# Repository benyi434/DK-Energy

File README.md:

# DK-Energy
DK Energy - Powerbank solar portátil con 18650, TP4056, MT3608, PIC16F887 y LCD 16x2. Proyecto integrador IPET 250 7mo año Electrónica.

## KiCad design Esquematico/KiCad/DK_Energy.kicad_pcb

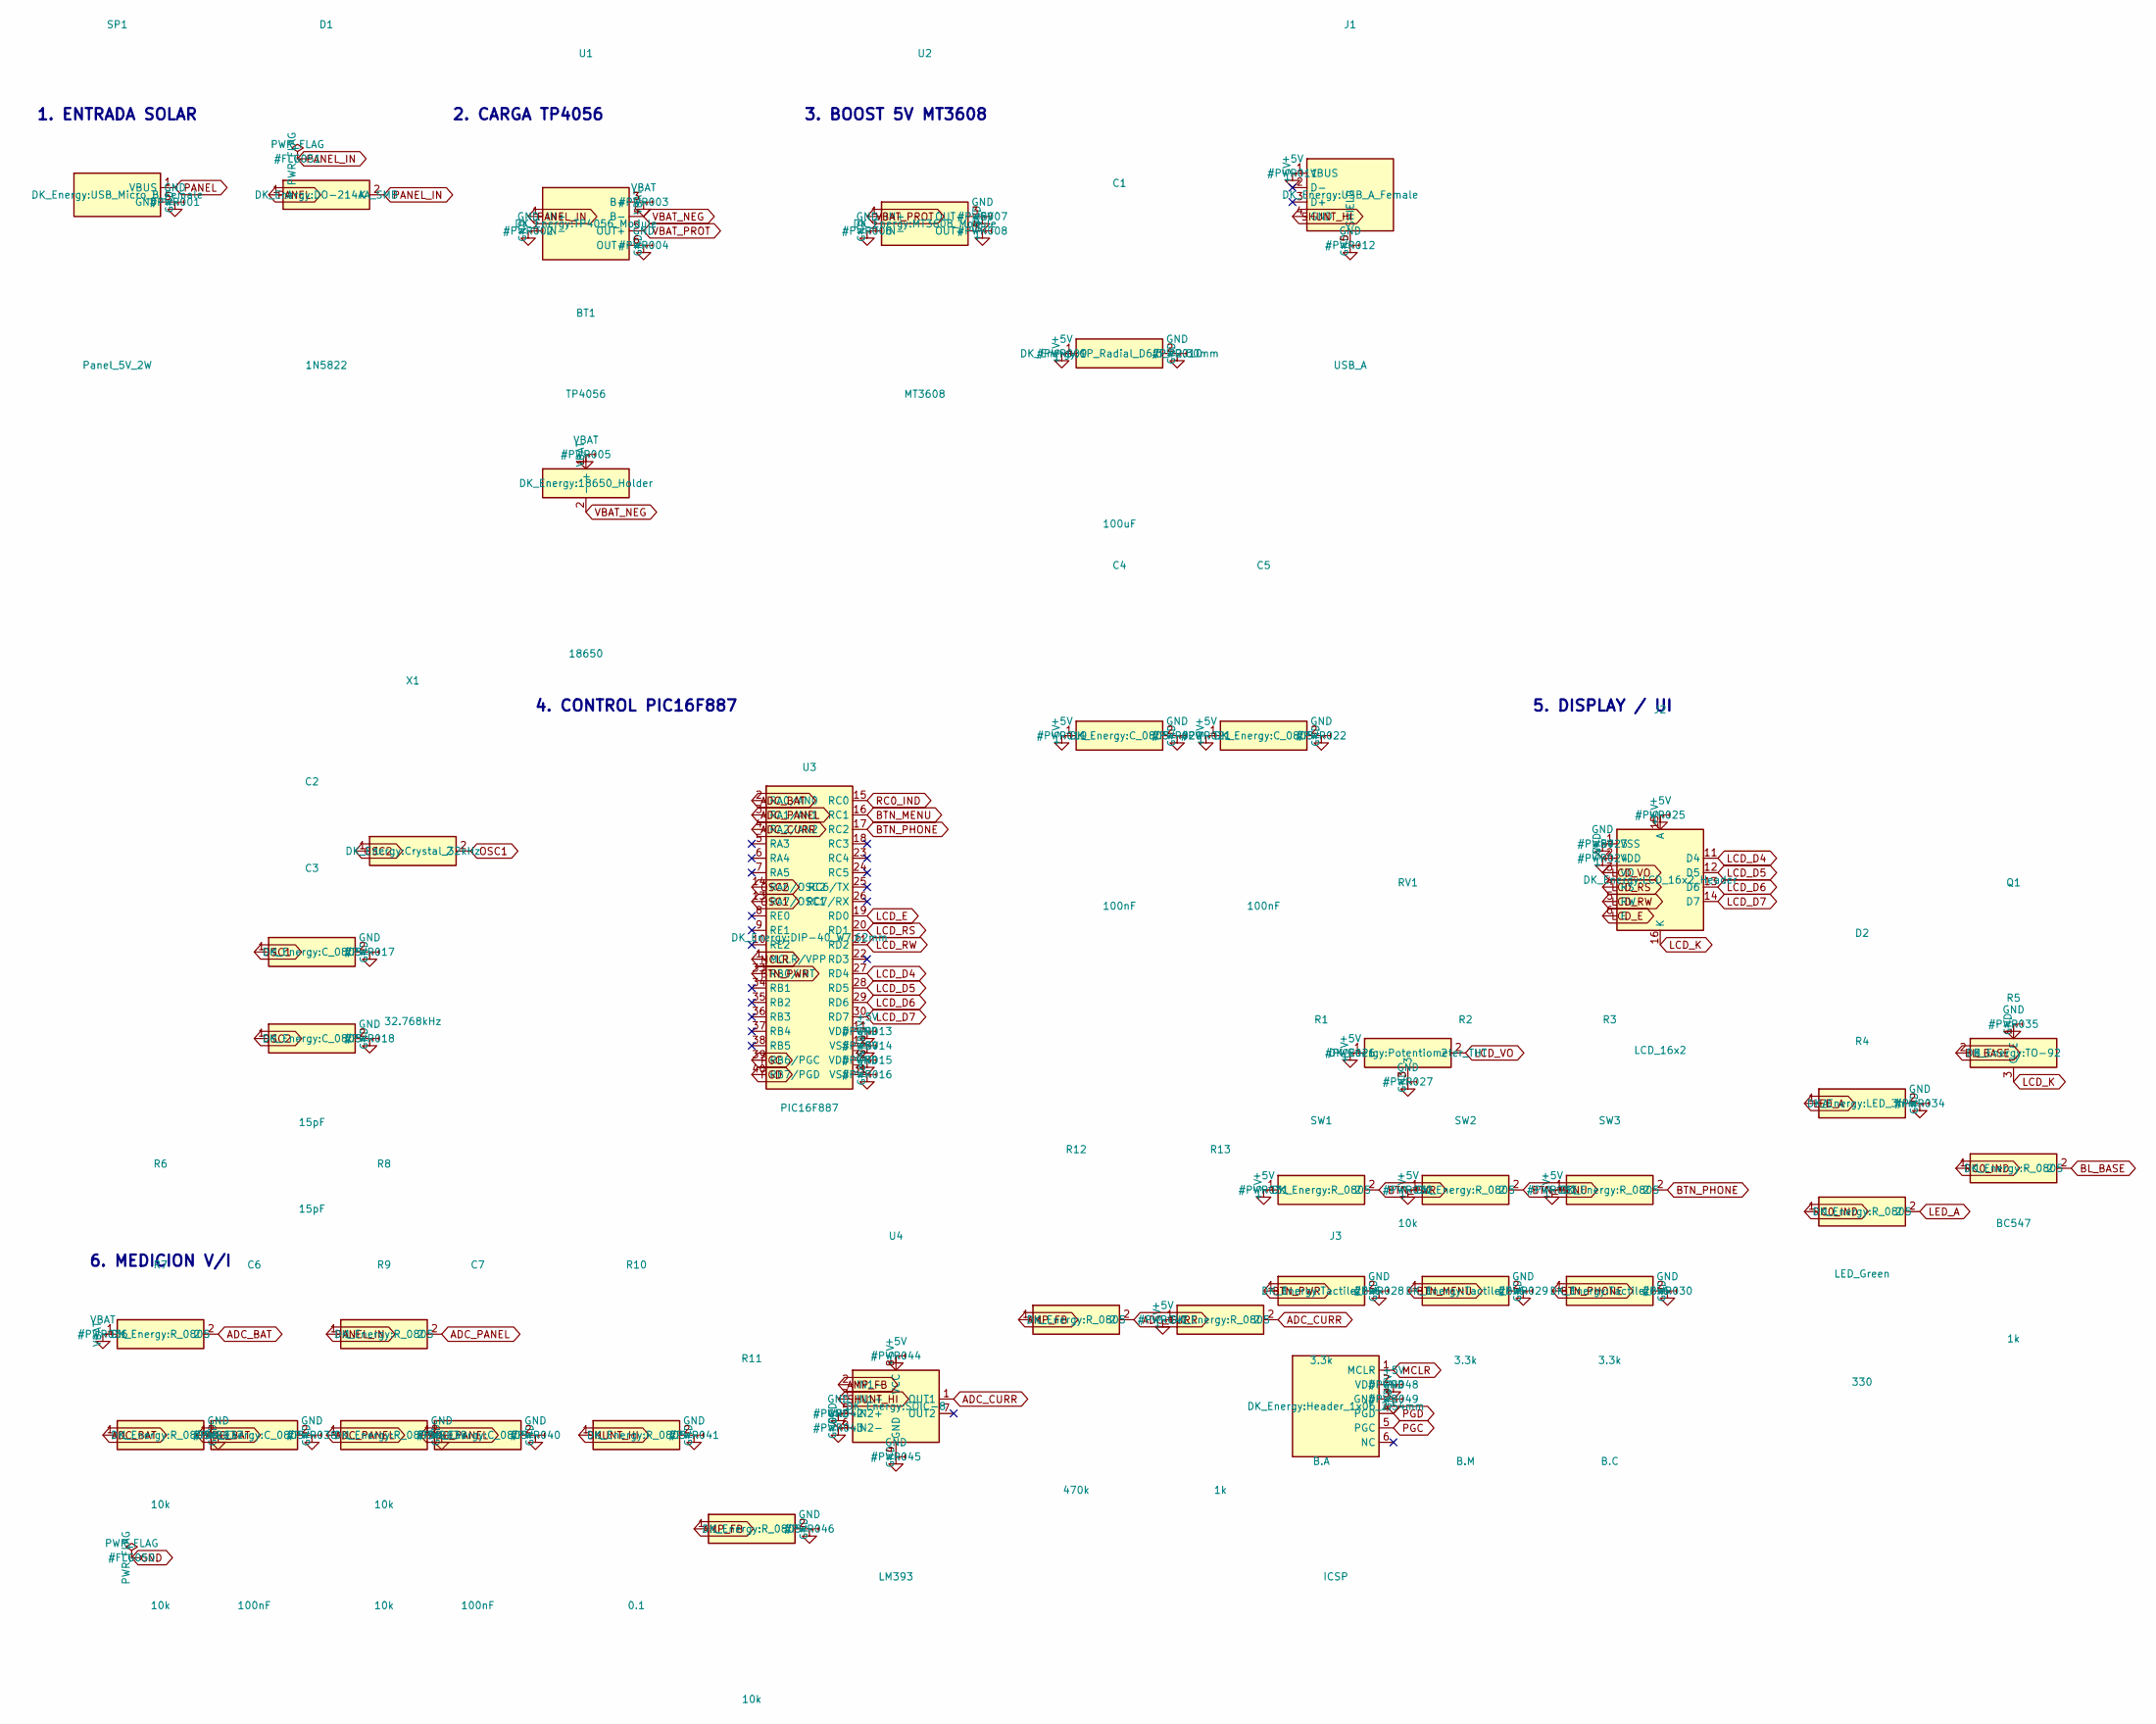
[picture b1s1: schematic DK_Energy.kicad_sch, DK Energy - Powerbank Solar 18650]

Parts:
BT1: 18650; 18650_Holder
C1: 100uF; CP_Radial_D6.3_P2.50mm
C2, C3: 15pF; C_0805
C4, C5, C6, C7: 100nF; C_0805
D1: 1N5822; DO-214AA_SMB
D2: LED_Green; LED_3mm
J1: USB_A; USB_A_Female
J2: LCD_16x2; LCD_16x2_Header
J3: ICSP; Header_1x06_2.54mm
Q1: BC547; TO-92
R1, R2, R3: 3.3k; R_0805
R4: 330; R_0805
R5, R13: 1k; R_0805
R6, R7, R8, R9, R11: 10k; R_0805
R10: 0.1; R_0805
R12: 470k; R_0805
RV1: 10k; Potentiometer_THT
SP1: Panel_5V_2W; USB_Micro_B_Female
SW1: B.A; Tactile_6x6
SW2: B.M; Tactile_6x6
SW3: B.C; Tactile_6x6
U1: TP4056; TP4056_Module
U2: MT3608; MT3608_Module
U3: PIC16F887; DIP-40_W7.62mm
U4: LM393; SOIC-8
X1: 32.768kHz; Crystal_32kHz

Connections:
+5V: C1.1, C4.1, C5.1, J1.1 (VBUS), J2.2 (VDD), J2.15 (A), J3.2 (VDD), R1.1, R2.1, R3.1, R13.1, RV1.1, U2.4 (OUT+), U3.11 (VDD), U3.32 (VDD), U4.8 (VCC)
ADC_BAT: C6.1, R6.2, R7.1, U3.2 (RA0/AN0)
ADC_CURR: R12.2, R13.2, U3.4 (RA2/AN2), U4.1 (OUT1)
ADC_PANEL: C7.1, R8.2, R9.1, U3.3 (RA1/AN1)
AMP_FB: R11.1, R12.1, U4.2 (IN1-)
BL_BASE: Q1.2 (B), R5.2
BTN_MENU: R2.2, SW2.1, SW2.3, U3.16 (RC1)
BTN_PHONE: R3.2, SW3.1, SW3.3, U3.17 (RC2)
BTN_PWR: R1.2, SW1.1, SW1.3, U3.33 (RB0/INT)
GND: C1.2, C2.2, C3.2, C4.2, C5.2, C6.2, C7.2, D2.2 (K), J1.5 (SHIELD), J1.6, J2.1 (VSS), J3.3 (GND), Q1.1 (E), R7.2, R9.2, R10.2, R11.2, RV1.3, SP1.5 (GND), SW1.2, SW1.4, SW2.2, SW2.4, SW3.2, SW3.4, U1.2 (IN-), U1.6 (OUT-), U2.2 (IN-), U2.3 (OUT-), U3.12 (VSS), U3.31 (VSS), U4.4 (GND), U4.5 (IN2+), U4.6 (IN2-)
LCD_D4: J2.11 (D4), U3.27 (RD4)
LCD_D5: J2.12 (D5), U3.28 (RD5)
LCD_D6: J2.13 (D6), U3.29 (RD6)
LCD_D7: J2.14 (D7), U3.30 (RD7)
LCD_E: J2.6 (E), U3.19 (RD0)
LCD_K: J2.16 (K), Q1.3 (C)
LCD_RS: J2.4 (RS), U3.20 (RD1)
LCD_RW: J2.5 (RW), U3.21 (RD2)
LCD_VO: J2.3 (VO), RV1.2
LED_A: D2.1 (A), R4.2
MCLR: J3.1 (MCLR), U3.1 (MCLR/VPP)
OSC1: C2.1, U3.13 (RA7/OSC1), X1.2
OSC2: C3.1, U3.14 (RA6/OSC2), X1.1
PANEL: D1.1 (A), SP1.1 (VBUS)
PANEL_IN: D1.2 (K), R8.1, U1.1 (IN+)
PGC: J3.5 (PGC), U3.39 (RB6/PGC)
PGD: J3.4 (PGD), U3.40 (RB7/PGD)
RC0_IND: R4.1, R5.1, U3.15 (RC0)
SHUNT_HI: J1.4 (GND), R10.1, U4.3 (IN1+)
VBAT: BT1.1 (+), R6.1, U1.3 (B+)
VBAT_NEG: BT1.2 (-), U1.4 (B-)
VBAT_PROT: U1.5 (OUT+), U2.1 (IN+)

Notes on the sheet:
1. ENTRADA SOLAR
2. CARGA TP4056
3. BOOST 5V MT3608
4. CONTROL PIC16F887
5. DISPLAY / UI
6. MEDICION V/I

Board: 2 copper layers, 41 parts (0 on the bottom side), 32 nets, no tracks yet.

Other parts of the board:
MH1, MH2, MH3, MH4: M3; MountingHole_3.2mm_M3
